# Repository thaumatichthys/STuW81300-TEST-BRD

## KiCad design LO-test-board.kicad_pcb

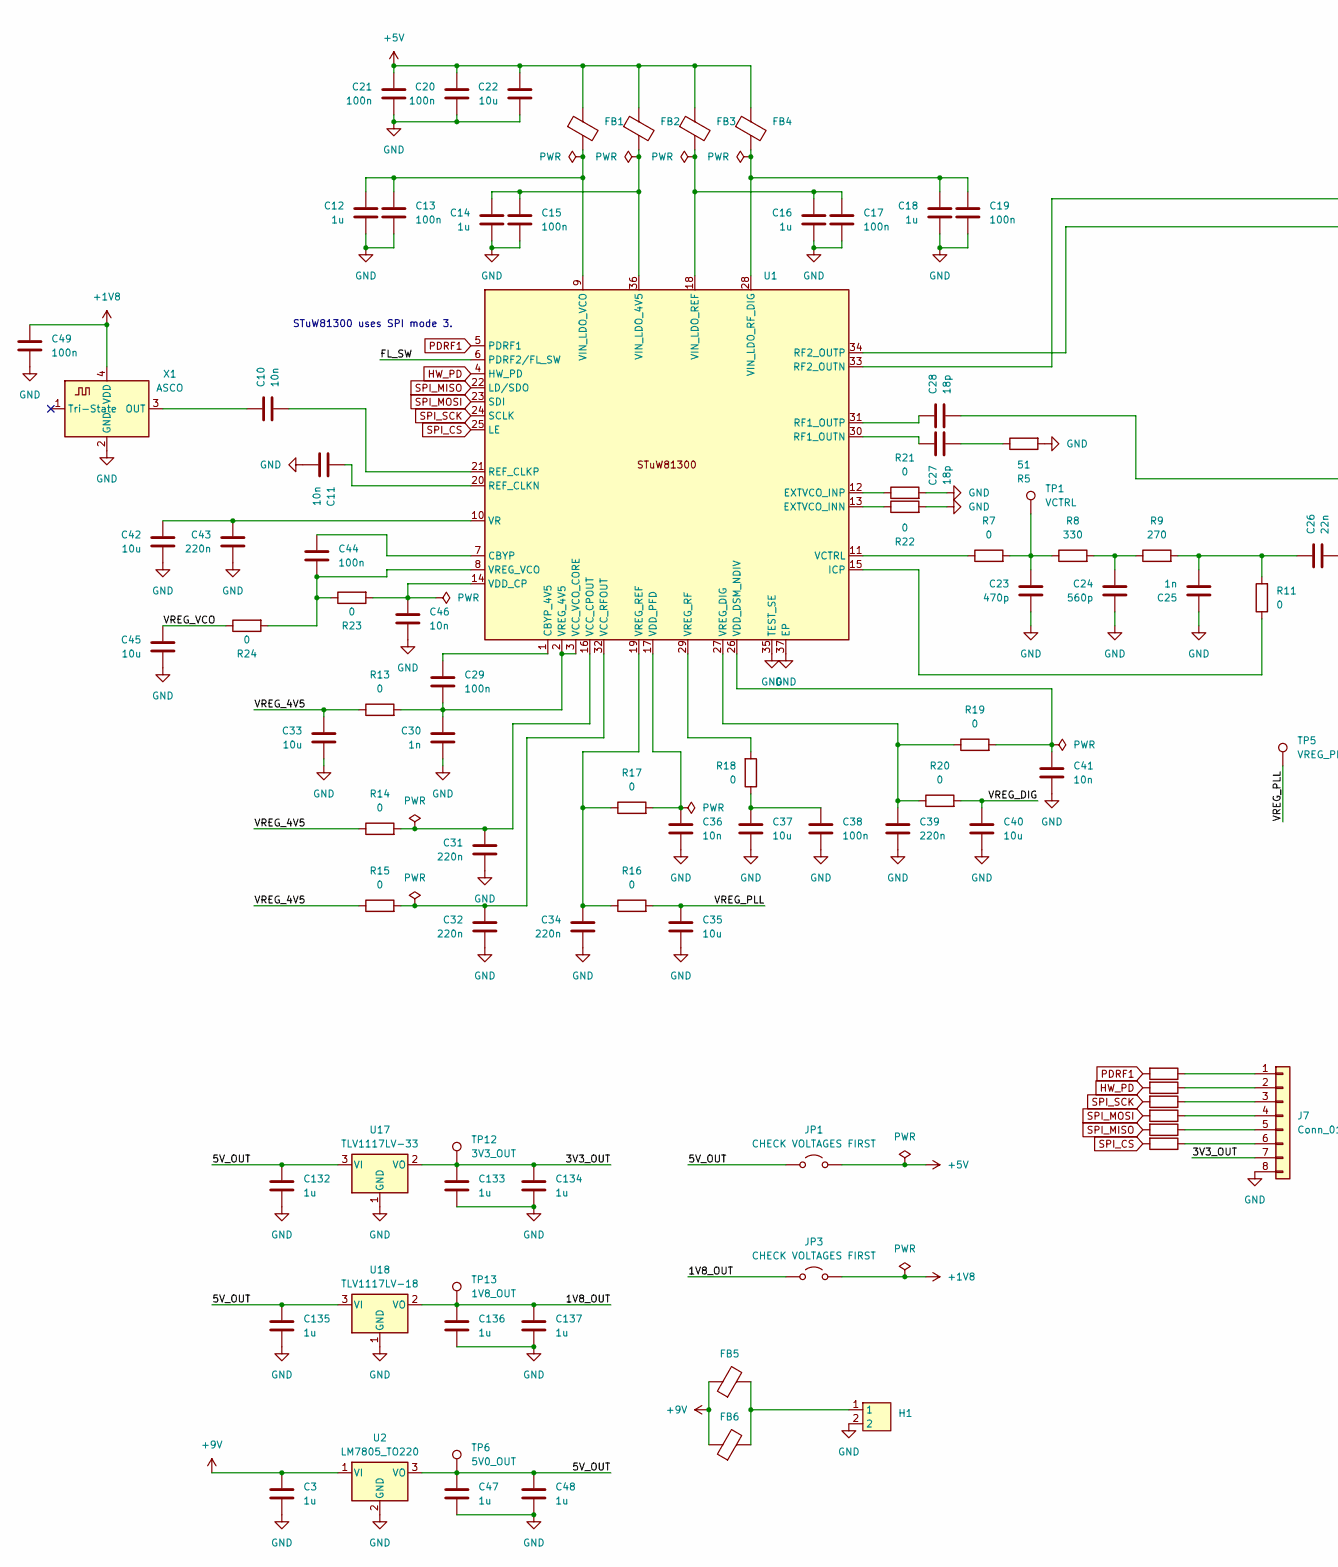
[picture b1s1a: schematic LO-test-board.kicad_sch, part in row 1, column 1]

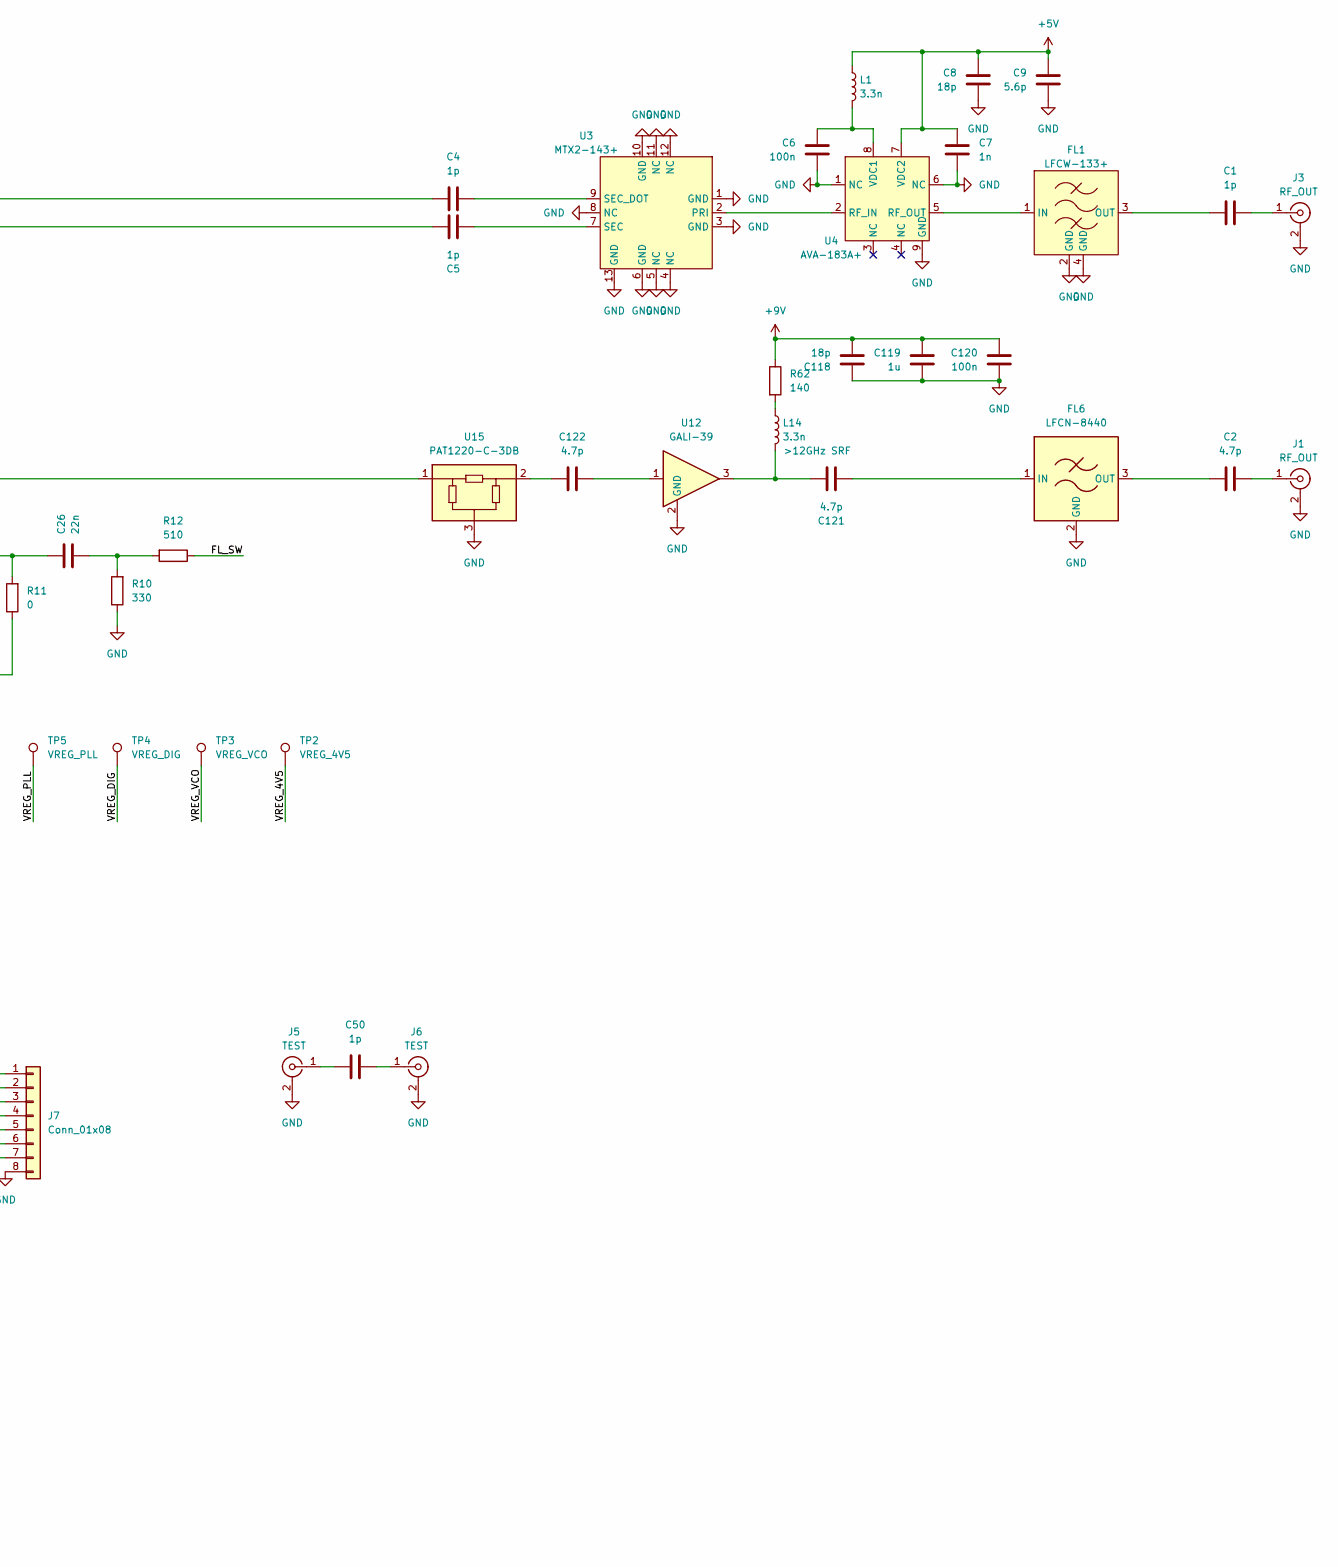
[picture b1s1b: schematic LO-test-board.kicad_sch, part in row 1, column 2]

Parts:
C1, C4, C5, C50: 1p; C_0402_1005Metric_Pad0.74x0.62mm_HandSolder
C2, C121, C122: 4.7p; C_0402_1005Metric_Pad0.74x0.62mm_HandSolder
C3, C12, C14, C16, C18, C47, C48, C119, C132, C133, C134, C135, C136, C137: 1u; C_0402_1005Metric_Pad0.74x0.62mm_HandSolder
C6, C13, C15, C17, C19, C20, C21, C29, C38, C44, C49, C120: 100n; C_0402_1005Metric_Pad0.74x0.62mm_HandSolder
C7, C25, C30: 1n; C_0402_1005Metric_Pad0.74x0.62mm_HandSolder
C8, C27, C28, C118: 18p; C_0402_1005Metric_Pad0.74x0.62mm_HandSolder
C9: 5.6p; C_0402_1005Metric_Pad0.74x0.62mm_HandSolder
C10, C11, C36, C41, C46: 10n; C_0402_1005Metric_Pad0.74x0.62mm_HandSolder
C22, C33, C35, C37, C40, C42, C45: 10u; C_0603_1608Metric_Pad1.08x0.95mm_HandSolder
C23: 470p; C_0402_1005Metric_Pad0.74x0.62mm_HandSolder
C24: 560p; C_0402_1005Metric_Pad0.74x0.62mm_HandSolder
C26: 22n; C_0402_1005Metric_Pad0.74x0.62mm_HandSolder
C31, C32, C34, C39, C43: 220n; C_0402_1005Metric_Pad0.74x0.62mm_HandSolder
FB1, FB2, FB3, FB4, FB5, FB6: MPZ1608S221ATA00; L_0603_1608Metric_Pad1.05x0.95mm_HandSolder
FL1: LFCW-133+; JC0603C-1
FL6: LFCN-8440; Filter_Mini-Circuits_FV1206-4
H1: 2-pin-spaced-header
J1, J3: RF_OUT; RF2-04A-T-00-50-G
J5, J6: TEST; RF2-04A-T-00-50-G
J7: Conn_01x08; PinHeader_1x08_P2.54mm_Vertical
JP1, JP3: CHECK VOLTAGES FIRST; SolderJumper-2_P1.3mm_Open_TrianglePad1.0x1.5mm
L1: 3.3n; L_0805_2012Metric
L14: 3.3n; L_0402_1005Metric_Pad0.77x0.64mm_HandSolder
R1, R2, R3, R4, R6, R12, R25: 510; R_0402_1005Metric_Pad0.72x0.64mm_HandSolder
R5: 51; R_0402_1005Metric_Pad0.72x0.64mm_HandSolder
R7, R11, R13, R14, R15, R16, R17, R18, R19, R20, R21, R22, R23, R24: 0; R_0402_1005Metric_Pad0.72x0.64mm_HandSolder
R8, R10: 330; R_0402_1005Metric_Pad0.72x0.64mm_HandSolder
R9: 270; R_0402_1005Metric_Pad0.72x0.64mm_HandSolder
R62: 140; R_1206_3216Metric
TP1: VCTRL; TestPoint_Pad_D1.0mm
TP2: VREG_4V5; TestPoint_Pad_D1.0mm
TP3: VREG_VCO; TestPoint_Pad_D1.0mm
TP4: VREG_DIG; TestPoint_Pad_D1.0mm
TP5: VREG_PLL; TestPoint_Pad_D1.0mm
TP6: 5V0_OUT; TestPoint_Pad_D1.0mm
TP12: 3V3_OUT; TestPoint_Pad_D1.0mm
TP13: 1V8_OUT; TestPoint_Pad_D1.0mm
U1: QFN-36-1EP_6x6mm_P0.5mm_EP4.1x4.1mm
U2: LM7805_TO220; TO-220-3_Vertical
U3: MTX2-143+; QFN-12-1EP_3x3mm_P0.51mm_EP1.45x1.45mm
U4: AVA-183A+; DQ849
U12: GALI-39; SOT-89-3
U15: PAT1220-C-3DB; RF_Attenuator_Susumu_PAT1220
U17: TLV1117LV-33; SOT-223-3_TabPin2
U18: TLV1117LV-18; SOT-223-3_TabPin2
X1: ASCO; Oscillator_SMD_ECS_2520MV-xxx-xx-4Pin_2.5x2.0mm

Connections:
+1V8: C49.1, JP3.2 (B), X1.4 (VDD)
+5V: C7.1, C8.1, C9.1, C20.1, C21.1, C22.1, FB1.1, FB2.1, FB3.1, FB4.1, JP1.2 (B), L1.1, U4.7 (VDC2)
+9V: C3.1, C118.2, C119.1, C120.2, FB5.1, FB6.1, R62.1, U2.1 (VI)
/1V8_OUT: C136.1, C137.1, JP3.1 (A), TP13.1, U18.2 (VO)
/3V3_OUT: C133.1, C134.1, J7.7, TP12.1, U17.2 (VO)
/5V_OUT: C47.1, C48.1, C132.1, C135.1, JP1.1 (A), TP6.1, U2.3 (VO), U17.3 (VI), U18.3 (VI)
/FL_SW: R12.1, U1.6 (PDRF2/FL_SW)
/VREG_4V5: C33.1, R13.1, R14.1, R15.1, TP2.1
/VREG_DIG: C40.1, R20.2, TP4.1
/VREG_PLL: C35.1, R16.2, TP5.1
/VREG_VCO: C45.1, R24.1, TP3.1
GND: C3.2, C6.2, C7.2, C8.2, C9.2, C11.2, C12.2, C13.2, C14.2, C15.2, C16.2, C17.2, C18.2, C19.2, C20.2, C21.2, C22.2, C23.2, C24.2, C25.1, C30.2, C31.2, C32.2, C33.2, C34.2, C35.2, C36.2, C37.2, C38.2, C39.2, C40.2, C41.2, C42.2, C43.2, C45.2, C46.2, C47.2, C48.2, C49.2, C118.1, C119.2, C120.1, C132.2, C133.2, C134.2, C135.2, C136.2, C137.2, FL1.2 (GND), FL1.4 (GND), FL6.2 (GND), FL6.4 (GND), H1.2, J1.2 (Ext), J3.2 (Ext), J5.2 (Ext), J6.2 (Ext), J7.8, R5.2, R10.1, R21.2, R22.2, U1.35 (TEST_SE), U1.37 (EP), U2.2 (GND), U3.1 (GND), U3.3 (GND), U3.4 (NC), U3.5 (NC), U3.6 (GND), U3.8 (NC), U3.10 (GND), U3.11 (NC), U3.12 (NC), U3.13 (GND), U4.1 (NC), U4.6 (NC), U4.9 (GND), U12.2 (GND), U15.3, U17.1 (GND), U18.1 (GND), X1.2 (GND)
HW_PD: R6.2, U1.4 (HW_PD)
unnamed: C23.1, R7.2, R8.1, TP1.1
unnamed: C24.1, R8.2, R9.1
unnamed: C25.2, C26.1, R9.2, R11.2
unnamed: C26.2, R10.2, R12.2
unnamed: C27.2, R5.1
unnamed: C28.2, U15.1
unnamed: C37.1, C38.1, R18.1
unnamed: C121.2, L14.2, U12.3
unnamed: C122.1, U12.1
unnamed: C122.2, U15.2
unnamed: FB5.2, FB6.2, H1.1
unnamed: FL1.1 (IN), U4.5 (RF_OUT)
unnamed: C1.1, FL1.3 (OUT)
unnamed: C121.1, FL6.1 (IN)
unnamed: C2.2, FL6.3 (OUT)
unnamed: C2.1, J1.1 (In)
unnamed: C1.2, J3.1 (In)
unnamed: C50.1, J5.1 (In)
unnamed: C50.2, J6.1 (In)
unnamed: J7.1, R25.1
unnamed: J7.2, R6.1
unnamed: J7.3, R2.1
unnamed: J7.4, R1.1
unnamed: J7.5, R3.1
unnamed: J7.6, R4.1
unnamed: L14.1, R62.2
unnamed: C44.2, U1.7 (CBYP)
unnamed: C29.1, U1.1 (CBYP_4V5)
unnamed: R22.1, U1.13 (EXTVCO_INN)
unnamed: R21.1, U1.12 (EXTVCO_INP)
unnamed: R11.1, U1.15 (ICP)
unnamed: C11.1, U1.20 (REF_CLKN)
unnamed: C10.2, U1.21 (REF_CLKP)
unnamed: C27.1, U1.30 (RF1_OUTN)
unnamed: C28.1, U1.31 (RF1_OUTP)
unnamed: C4.1, U1.33 (RF2_OUTN)
unnamed: C5.1, U1.34 (RF2_OUTP)
unnamed: C31.1, R14.2, U1.16 (VCC_CPOUT)
unnamed: C32.1, R15.2, U1.32 (VCC_RFOUT)
unnamed: C29.2, C30.1, R13.2, U1.2 (VREG_4V5), U1.3 (VCC_VCO_CORE)
unnamed: R7.1, U1.11 (VCTRL)
unnamed: C46.1, R23.2, U1.14 (VDD_CP)
unnamed: C41.1, R19.2, U1.26 (VDD_DSM_NDIV)
unnamed: C36.1, R17.2, U1.17 (VDD_PFD)
unnamed: C14.1, C15.1, FB2.2, U1.36 (VIN_LDO_4V5)
unnamed: C16.1, C17.1, FB3.2, U1.18 (VIN_LDO_REF)
unnamed: C18.1, C19.1, FB4.2, U1.28 (VIN_LDO_RF_DIG)
unnamed: C12.1, C13.1, FB1.2, U1.9 (VIN_LDO_VCO)
unnamed: C42.1, C43.1, U1.10 (VR)
unnamed: C39.1, R19.1, R20.1, U1.27 (VREG_DIG)
unnamed: C34.1, R16.1, R17.1, U1.19 (VREG_REF)
unnamed: R18.2, U1.29 (VREG_RF)
unnamed: C44.1, R23.1, R24.2, U1.8 (VREG_VCO)
unnamed: U3.2 (PRI), U4.2 (RF_IN)
unnamed: C5.2, U3.7 (SEC)
unnamed: C4.2, U3.9 (SEC_DOT)
unnamed: C6.1, L1.2, U4.8 (VDC1)
unnamed: C10.1, X1.3 (OUT)
PDRF1: R25.2, U1.5 (PDRF1)
SPI_CS: R4.2, U1.25 (LE)
SPI_MISO: R3.2, U1.22 (LD/SDO)
SPI_MOSI: R1.2, U1.23 (SDI)
SPI_SCK: R2.2, U1.24 (SCLK)

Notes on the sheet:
STuW81300 uses SPI mode 3.

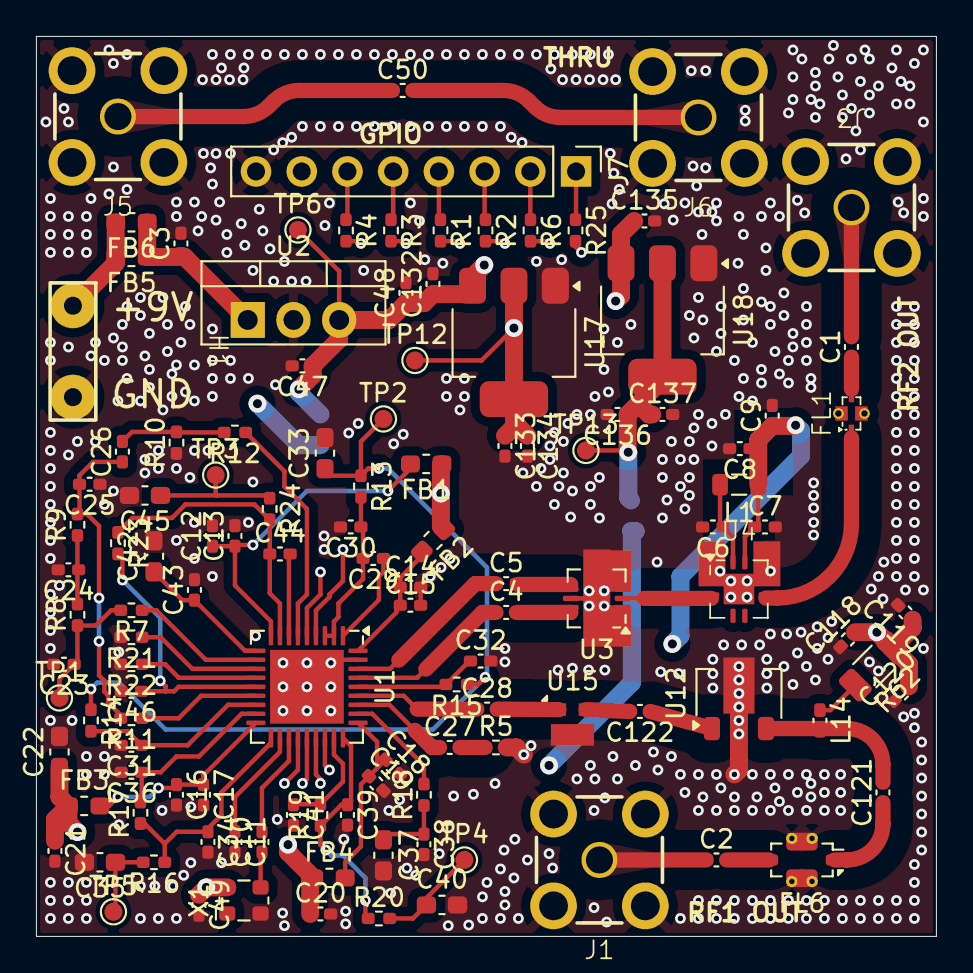
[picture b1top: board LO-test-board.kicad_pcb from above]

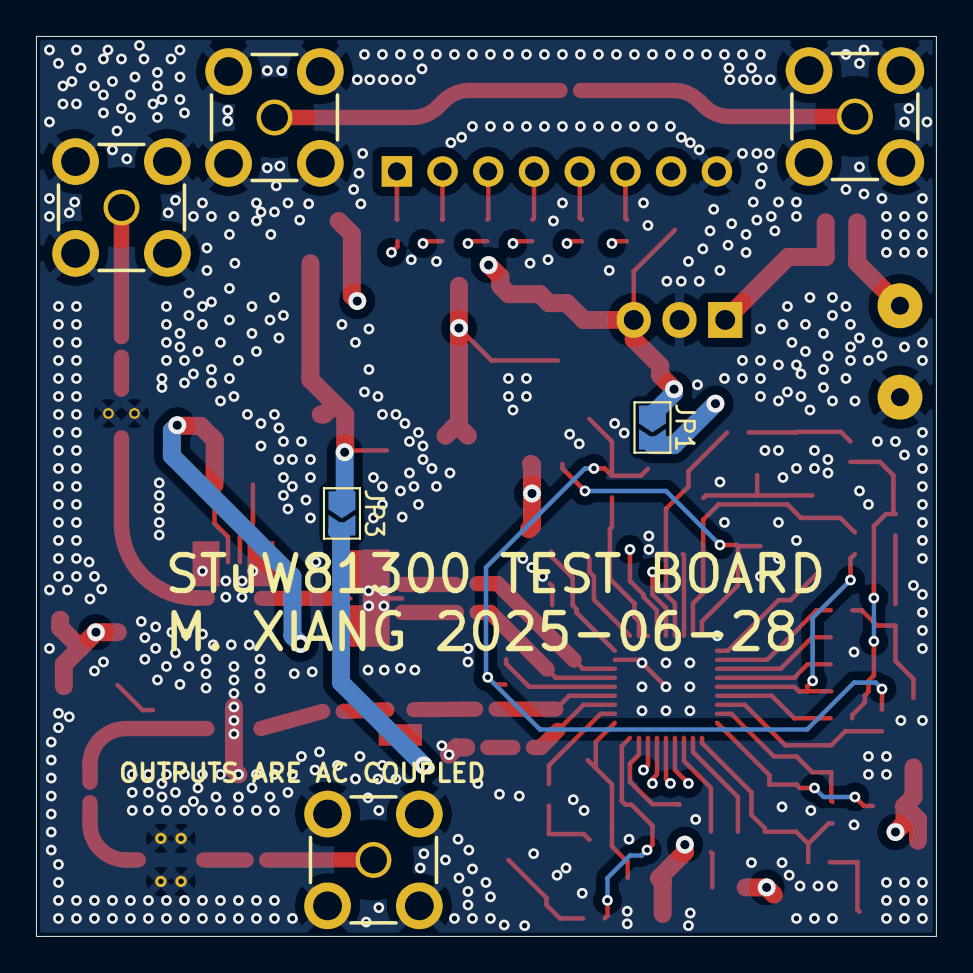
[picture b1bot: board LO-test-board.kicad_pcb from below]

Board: 6 copper layers, 50.0 x 50.0 mm, 122 parts (2 on the bottom side), 76 nets.

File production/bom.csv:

Designator,Footprint,Quantity,Value,LCSC Part #
"C1, C4, C5, C50",0402,4,1p,
"C10, C11, C36, C41, C46",0402,5,10n,
"C118, C27, C28, C8",0402,4,18p,
"C119, C12, C132, C133, C134, C135, C136, C137, C14, C16, C18, C3, C47, C48",0402,14,1u,
"C120, C13, C15, C17, C19, C20, C21, C29, C38, C44, C49, C6",0402,12,100n,
"C121, C122, C2",0402,3,4.7p,
"C22, C33, C35, C37, C40, C42, C45",0603,7,10u,
C23,0402,1,470p,
C24,0402,1,560p,
"C25, C30, C7",0402,3,1n,
C26,0402,1,22n,
"C31, C32, C34, C39, C43",0402,5,220n,
C9,0402,1,5.6p,
"FB1, FB2, FB3, FB4, FB5, FB6",0603,6,MPZ1608S221ATA00,
FL1,JC0603C-1,1,LFCW-133+,
FL6,Filter_Mini-Circuits_FV1206-4,1,LFCN-8440,
H1,2-pin-spaced-header,1,~,
"J1, J3",RF2-04A-T-00-50-G,2,RF_OUT,
"J5, J6",RF2-04A-T-00-50-G,2,TEST,
J7,PinHeader_1x08_P2.54mm_Vertical,1,Conn_01x08,
"JP1, JP3",SolderJumper-2_P1.3mm_Open_TrianglePad1.0x1.5mm,2,CHECK VOLTAGES FIRST,
L1,0805,1,3.3n,
L14,0402,1,3.3n,
"R1, R12, R2, R25, R3, R4, R6",0402,7,510,
"R10, R8",0402,2,330,
"R11, R13, R14, R15, R16, R17, R18, R19, R20, R21, R22, R23, R24, R7",0402,14,0,
R5,0402,1,51,
R62,1206,1,140,
R9,0402,1,270,
TP1,TestPoint_Pad_D1.0mm,1,VCTRL,
TP12,TestPoint_Pad_D1.0mm,1,3V3_OUT,
TP13,TestPoint_Pad_D1.0mm,1,1V8_OUT,
TP2,TestPoint_Pad_D1.0mm,1,VREG_4V5,
TP3,TestPoint_Pad_D1.0mm,1,VREG_VCO,
TP4,TestPoint_Pad_D1.0mm,1,VREG_DIG,
TP5,TestPoint_Pad_D1.0mm,1,VREG_PLL,
TP6,TestPoint_Pad_D1.0mm,1,5V0_OUT,
U1,QFN-36-1EP_6x6mm_P0.5mm_EP4.1x4.1mm,1,~,
U12,SOT-89-3,1,GALI-39,
U15,RF_Attenuator_Susumu_PAT1220,1,PAT1220-C-3DB,
U17,SOT-223-3_TabPin2,1,TLV1117LV-33,
U18,SOT-223-3_TabPin2,1,TLV1117LV-18,
U2,TO-220-3_Vertical,1,LM7805_TO220,
U3,QFN-12-1EP_3x3mm_P0.51mm_EP1.45x1.45mm,1,MTX2-143+,
U4,DQ849,1,AVA-183A+,
X1,Oscillator_SMD_ECS_2520MV-xxx-xx-4Pin_2.5x2.0mm,1,ASCO,

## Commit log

2025-06-28 updated schematic pdf
